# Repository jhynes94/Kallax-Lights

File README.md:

# Kallax-Lights
Lighting for Ikea Kallax Shelf units

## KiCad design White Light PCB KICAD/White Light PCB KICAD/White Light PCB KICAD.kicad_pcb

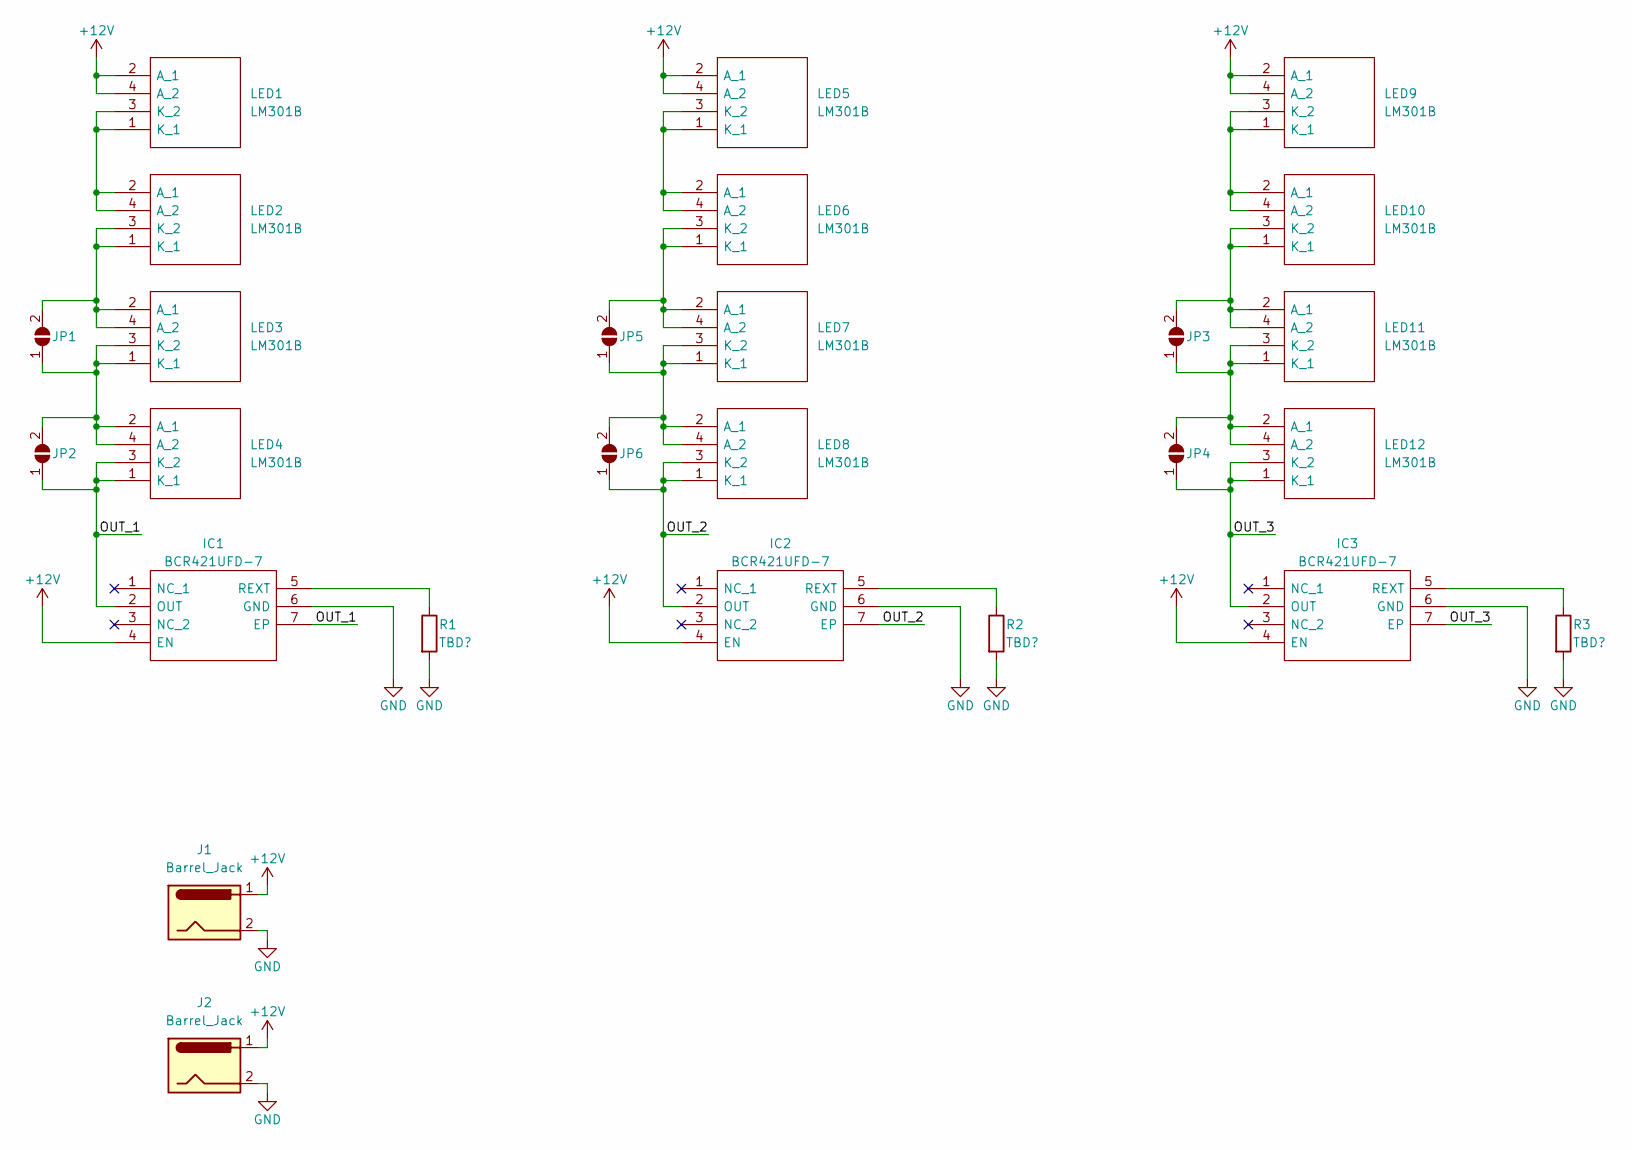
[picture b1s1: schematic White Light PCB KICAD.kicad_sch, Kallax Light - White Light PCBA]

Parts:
IC1, IC2, IC3: BCR421UFD-7; BCR421UFD7; Manufacturer_Part_Number BCR421UFD-7; Mouser Part Number 621-BCR421UFD-7
J1, J2: Barrel_Jack; BarrelJack_CUI_PJ-102AH_Horizontal; Manufacturer_Part_Number PJ-102AH; Mouser Testing Price/St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 0.50
JP1, JP2, JP3, JP4, JP5, JP6: SolderJumper_2_Open; SolderJumper-2_P1.3mm_Open_TrianglePad1.0x1.5mm
LED1, LED2, LED3, LED4, LED5, LED6, LED7, LED8, LED9, LED10, LED11, LED12: LM301B; Manufacturer_Part_Number LM301B; Mouser Testing Price/St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 0.11
R1, R2, R3: TBD?; R_1206_3216Metric_Pad1.30x1.75mm_HandSolder; Mouser Testing Price/St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 .08

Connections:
+12V: IC1.4 (EN), IC2.4 (EN), IC3.4 (EN), J1.1, J2.1, LED1.2 (A_1), LED1.4 (A_2), LED5.2 (A_1), LED5.4 (A_2), LED9.2 (A_1), LED9.4 (A_2)
/OUT_1: IC1.2 (OUT), IC1.7 (EP), JP2.1 (A), LED4.1 (K_1), LED4.3 (K_2)
/OUT_2: IC2.2 (OUT), IC2.7 (EP), JP6.1 (A), LED8.1 (K_1), LED8.3 (K_2)
/OUT_3: IC3.2 (OUT), IC3.7 (EP), JP4.1 (A), LED12.1 (K_1), LED12.3 (K_2)
GND: IC1.6 (GND), IC2.6 (GND), IC3.6 (GND), J1.2, J2.2, R1.2, R2.2, R3.2
unnamed: IC1.5 (REXT), R1.1
unnamed: IC2.5 (REXT), R2.1
unnamed: IC3.5 (REXT), R3.1
unnamed: JP1.1 (A), JP2.2 (B), LED3.1 (K_1), LED3.3 (K_2), LED4.2 (A_1), LED4.4 (A_2)
unnamed: JP1.2 (B), LED2.1 (K_1), LED2.3 (K_2), LED3.2 (A_1), LED3.4 (A_2)
unnamed: JP3.1 (A), JP4.2 (B), LED11.1 (K_1), LED11.3 (K_2), LED12.2 (A_1), LED12.4 (A_2)
unnamed: JP3.2 (B), LED10.1 (K_1), LED10.3 (K_2), LED11.2 (A_1), LED11.4 (A_2)
unnamed: JP5.1 (A), JP6.2 (B), LED7.1 (K_1), LED7.3 (K_2), LED8.2 (A_1), LED8.4 (A_2)
unnamed: JP5.2 (B), LED6.1 (K_1), LED6.3 (K_2), LED7.2 (A_1), LED7.4 (A_2)
unnamed: LED1.1 (K_1), LED1.3 (K_2), LED2.2 (A_1), LED2.4 (A_2)
unnamed: LED5.1 (K_1), LED5.3 (K_2), LED6.2 (A_1), LED6.4 (A_2)
unnamed: LED9.1 (K_1), LED9.3 (K_2), LED10.2 (A_1), LED10.4 (A_2)

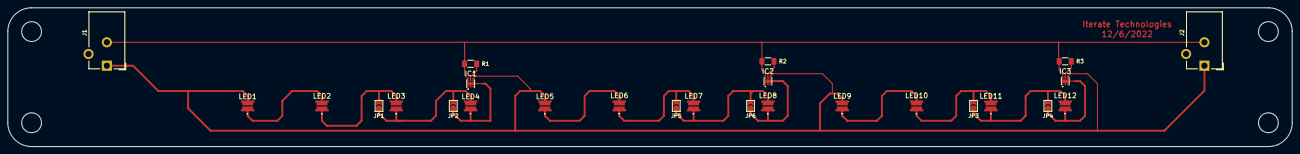
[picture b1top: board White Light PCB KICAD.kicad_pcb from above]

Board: 2 copper layers, 329.2 x 35.6 mm, 26 parts (0 on the bottom side), 17 nets.

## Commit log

2022-12-13 Production Build in early December 2022
